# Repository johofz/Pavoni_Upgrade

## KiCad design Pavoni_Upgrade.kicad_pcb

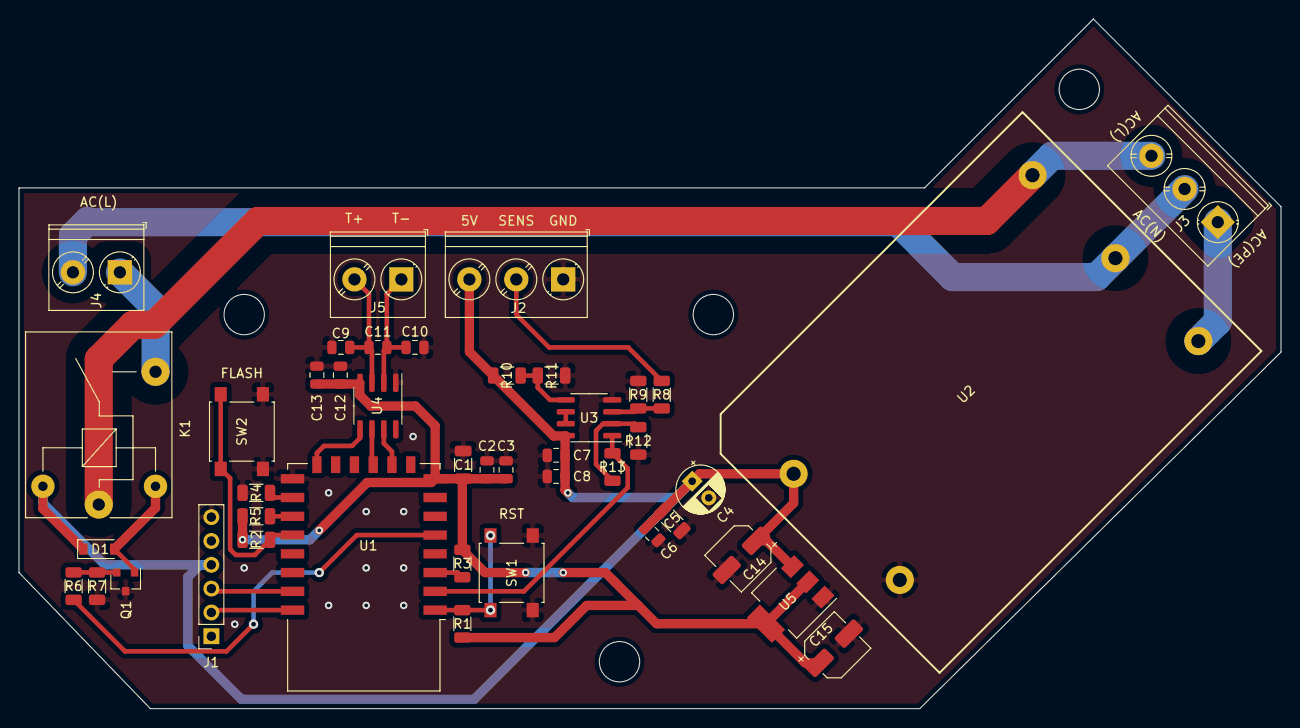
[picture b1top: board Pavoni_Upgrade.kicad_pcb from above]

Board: 2 copper layers, 134.5 x 73.5 mm, 47 parts (0 on the bottom side), 28 nets.

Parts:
C1, C5: 1u; C_1206_3216Metric
C2, C6, C7, C11, C12: 100n; C_0805_2012Metric
C3: 10u; C_0805_2012Metric
C4: 10u; CP_Radial_D5.0mm_P2.50mm
C8, C9, C10, C13: 10n; C_0805_2012Metric
C14, C15: 10u; CP_Elec_5x3
D1: D; D_SOD-123
H1, H2, H3, H4: MountingHole; MountingHole_4.3mm_M4_DIN965
J1: SERIAL; PinSocket_1x06_P2.54mm_Vertical
J2: P_SENSOR; TerminalBlock_Phoenix_PT-1,5-3-5.0-H_1x03_P5.00mm_Horizontal
J3: AC_IN; TerminalBlock_Phoenix_PT-1,5-3-5.0-H_1x03_P5.00mm_Horizontal
J4: HEATER_AC_L; TerminalBlock_Phoenix_PT-1,5-2-5.0-H_1x02_P5.00mm_Horizontal
J5: TEMP_CONN; TerminalBlock_Phoenix_PT-1,5-2-5.0-H_1x02_P5.00mm_Horizontal
K1: SANYOU_SRD_Form_A; Relay_SPST_SANYOU_SRD_Series_Form_A
Q1: Q_NPN_Darlington_CBE; SOT-23
R1, R2, R3, R4, R5, R6, R7, R9, R10, R11, R13: 10k; R_1206_3216Metric
R8, R12: 50k; R_1206_3216Metric
SW1, SW2: BUTTON; SW_SPST_B3S-1000
U1: ESP-12F; ESP-12E
U2: LH05-10B05
U3: Opamp_Dual_Generic; SOIC-8_3.9x4.9mm_P1.27mm
U4: MAX31855KASA; SOIC-8_3.9x4.9mm_P1.27mm
U5: NCP1117-12_SOT223; SOT-223-3_TabPin2

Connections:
+3V3: C1.1, C2.1, C3.1, C12.1, C13.1, C15.1, R1.1, R2.1, R3.1, R5.1, U1.8, U4.4, U5.2
+5V: C4.1, C5.1, C6.1, C7.1, C8.1, C14.1, D1.1, J1.4, J2.3, K1.5, R10.2, U2.4, U3.8, U5.3
/AC_L_IN: J3.3, K1.1, U2.1
/AC_L_OUT: J4.1, K1.3
/AC_N_IN: J3.2, J4.2, U2.2
/AC_PE_IN: J3.1, U2.3
/ESP-12/(GPIO2): R5.2, U1.17
/ESP-12/(GPIO15): R4.1, U1.16
/ESP-12/ADC_IN: R13.2, U1.2, U3.1
/ESP-12/BOOT: R2.2, SW2.2, U1.18
/ESP-12/CS: U1.11, U4.6
/ESP-12/EN: R3.2, U1.3
/ESP-12/MISO: U1.10, U4.7
/ESP-12/RST: R1.2, SW1.2, U1.1
/ESP-12/RXD: J1.3, U1.21
/ESP-12/SCLK: U1.14, U4.5
/ESP-12/TXD: J1.2, U1.22
/Load/RELAY_SIG_IN: R6.2, U1.5
/SENS_IN: J2.2, R8.2
/T+: C9.1, C11.1, J5.2, U4.3
/T-: C10.1, C11.2, J5.1, U4.2
GND: C1.2, C2.2, C3.2, C4.2, C5.2, C6.2, C7.2, C8.2, C9.2, C10.2, C12.2, C13.2, C14.2, C15.2, J1.6, J2.1, Q1.3, R4.2, R7.1, R9.1, R11.2, R12.1, SW1.1, SW2.1, U1.15, U2.5, U3.4, U4.1, U5.1
unnamed: D1.2, K1.2, Q1.1
unnamed: Q1.2, R6.1, R7.2
unnamed: R8.1, R9.2, U3.3
unnamed: R10.1, R11.1, U3.5
unnamed: R12.2, R13.1, U3.2
unnamed: U3.6, U3.7
